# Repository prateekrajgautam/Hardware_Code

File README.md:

# Hardware_Code

## Use arduino to program FTDI/Serial devices

### First config Arduino as and of the three

1. Connect RESET pin to GND. This is easiest.

2. Remove the Atmel Chip

3. upload this sketch

   ```cpp
   void setup(){
     pinMode(0,INPUT);
     pinMode(1,INPUT);
   }
   void loop(){
   }
   ```

### Second connect with external board

1. connect power pins

2. then connect RX (arduino) pin to RX (external board)

3. and TX (arduino)  pin to TX(external board)

# Uploading code to ESPWROOM32 ESP8266

1. press **EN** to reset,
2. compile and upload and when show `connecting .................`
3. press **Boot** and release.

platformio config for esp32-wroom-32 is

```ini
[env:esp_wroom_02]
platform = espressif32
board = nodemcu-32s
framework = arduino
monitor_speed = 115200
lib_deps = yoursunny/WifiEspNow@^0.0.20201226
```

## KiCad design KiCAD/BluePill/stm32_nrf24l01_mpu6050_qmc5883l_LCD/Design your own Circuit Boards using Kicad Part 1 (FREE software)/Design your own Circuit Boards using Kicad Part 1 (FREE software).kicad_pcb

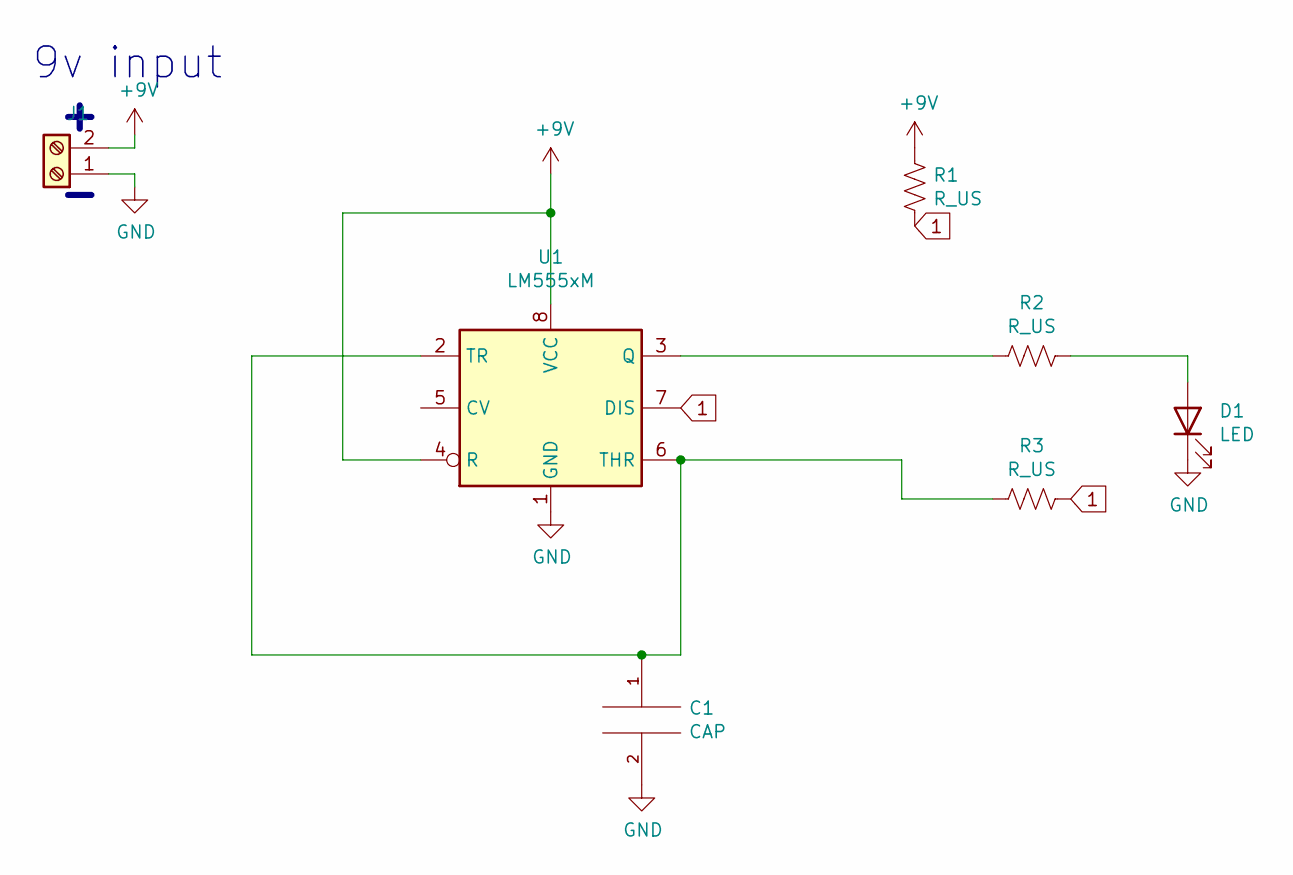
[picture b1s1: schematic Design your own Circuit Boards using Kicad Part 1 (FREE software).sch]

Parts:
C1: CAP; CP_Axial_L10.0mm_D4.5mm_P15.00mm_Horizontal
D1: LED; LED_D5.0mm
J1: Screw_Terminal_01x02; TerminalBlock_bornier-2_P5.08mm
R1, R2, R3: R_US; R_Axial_DIN0309_L9.0mm_D3.2mm_P5.08mm_Vertical
U1: LM555xM; DIP-8_W7.62mm_LongPads

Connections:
1: R1.2, R3.1, U1.7 (DIS)
+9V: J1.2, R1.1, U1.4 (R), U1.8 (VCC)
GND: C1.2, D1.1 (K), J1.1, U1.1 (GND)
unnamed: C1.1, R3.2, U1.2 (TR), U1.6 (THR)
unnamed: D1.2 (A), R2.1
unnamed: R2.2, U1.3 (Q)

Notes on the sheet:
9v input

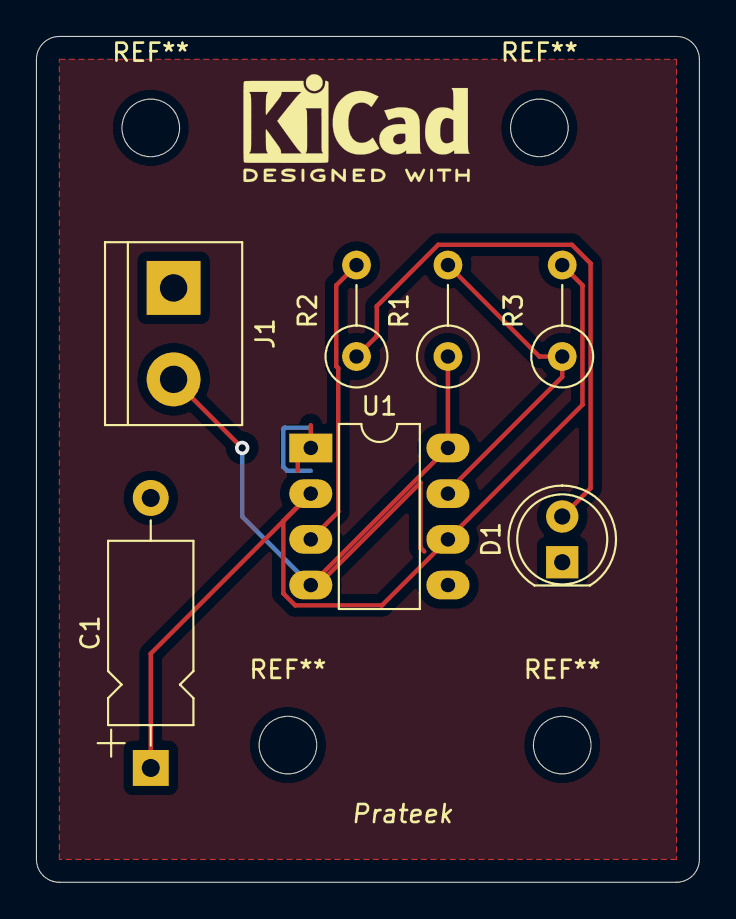
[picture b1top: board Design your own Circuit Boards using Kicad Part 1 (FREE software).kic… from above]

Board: 2 copper layers, 36.8 x 47.0 mm, 7 parts (0 on the bottom side), 6 nets.

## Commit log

2021-02-08 initializing code with basic platformio RX and TX for nrf24l01 using arduinoUNO and STM32
2021-02-09 BASIC code for RX and TX using nrf24l01 working on UNO and STM32
2021-02-10 unification of basic code, but now it is not interoperating with stm32Tx with UnoRx and viceverse, unoTx works with unoRx and StmTx with StmRx, some how the beacon array is not properly received due 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
2021-02-10 uint_16 makes it working across uno and stm32 tx and rx
2021-02-10 bootloader comfig via usb dfu for stm
2021-02-12 transmitting phi correctly servo some times work sometimes not
2021-02-14 esp8266 rssi ap and sta code with rssi value
2021-02-14 ESP-NOW Tx and Rx with mack detection
2021-02-15 ESP01 code working and uploading via nano
2021-02-16 esp01 tx esp8266 tx and esp8266 rx configuration
2021-02-16 xbee resources added
2021-03-18 ESP32CAM code
2021-06-24 esp8266 LED indicator range maxrssi to 10db below
